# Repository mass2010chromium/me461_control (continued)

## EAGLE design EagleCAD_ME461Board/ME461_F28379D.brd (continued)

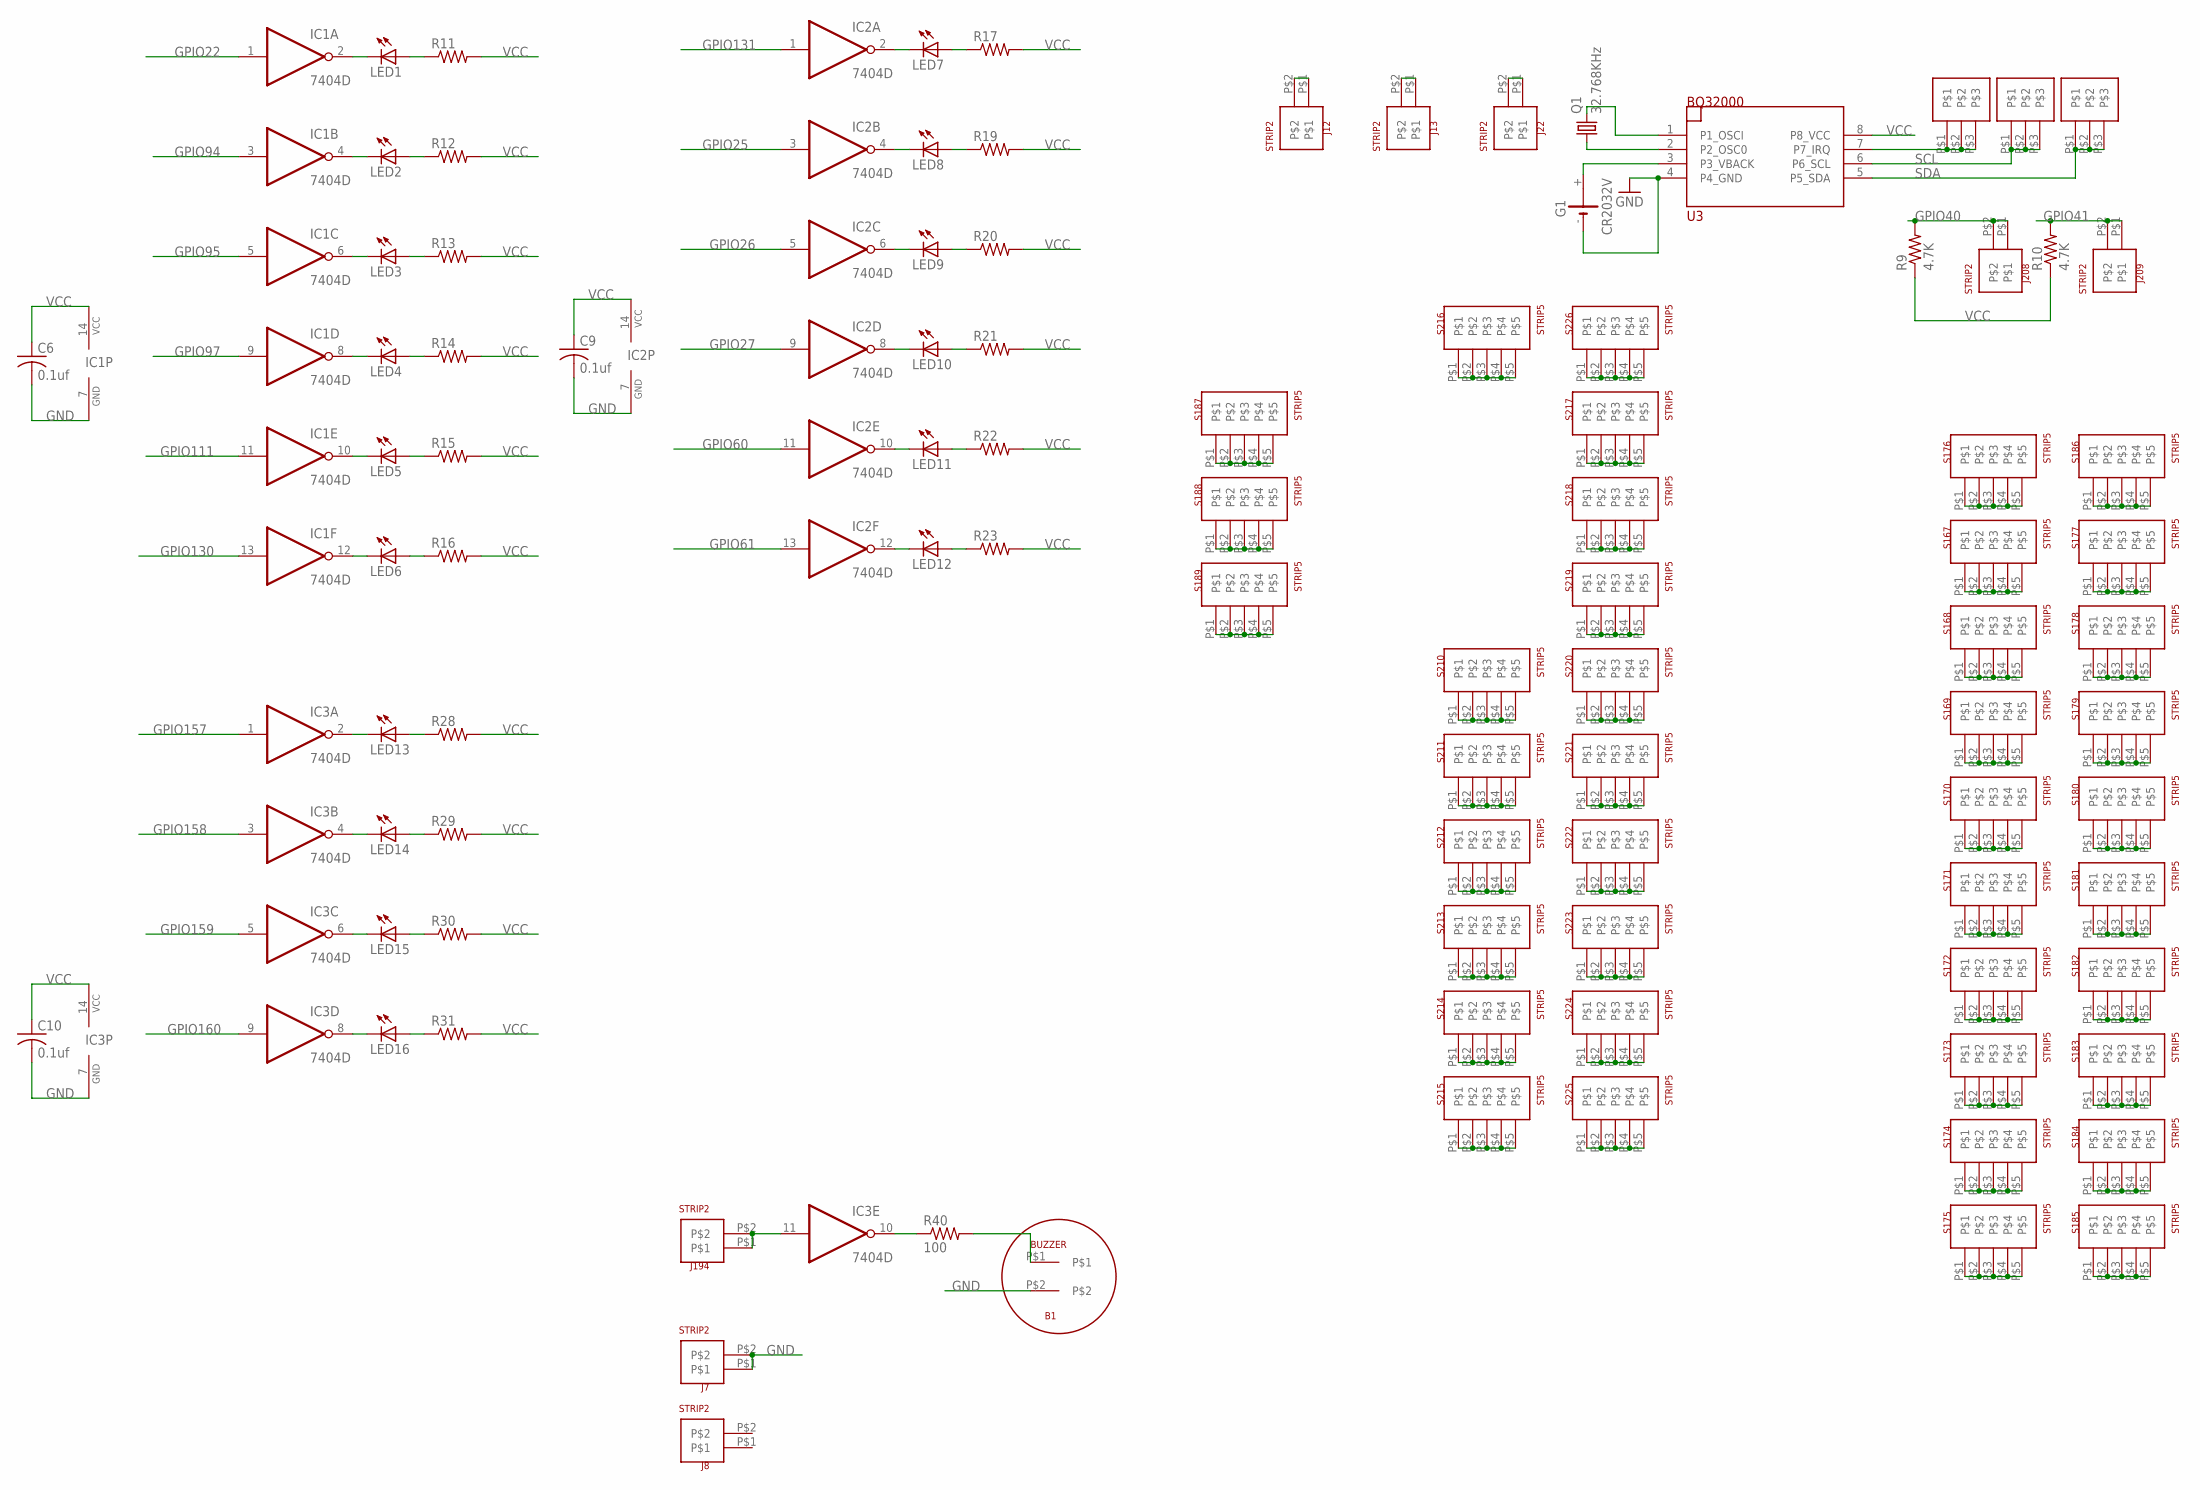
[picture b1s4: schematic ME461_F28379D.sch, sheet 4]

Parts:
B1: BUZZER
C6, C9, C10: 0.1uf; C1206
G1: CR2032V
IC1, IC2, IC3: 7404D; SO14
J1, J2, J3: STRIP3
J7, J8, J12, J13, J22, J194, J208, J209: STRIP2
LED1, LED2, LED3, LED4, LED5, LED6, LED7, LED8, LED9, LED10, LED11, LED12, LED13, LED14, LED15, LED16: LEDCHIPLED_1206; CHIPLED_1206
Q1: 32.768KHz; TC26H
R9, R10: 4.7K; R1206
R11, R12, R13, R14, R15, R16, R17, R19, R20, R21, R22, R23, R28, R29, R30, R31: R-US_R1206; R1206
R40: 100; R1206
S167, S168, S169, S170, S171, S172, S173, S174, S175, S176, S177, S178, S179, S180, S181, S182, S183, S184, S185, S186, S187, S188, S189, S210, S211, S212, S213, S214, S215, S216, S217, S218, S219, S220, S221, S222, S223, S224, S225, S226: STRIP5
U3: BQ32000; SO08

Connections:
GND: B1.P$2, C6.2, C9.2, C10.2, G1.-, IC1.7 (GND), IC2.7 (GND), IC3.7 (GND), J7.P$1, J7.P$2, U3.4 (P4_GND); also elsewhere on the board
GPIO22: IC1.1 (I); also elsewhere on the board
GPIO25: IC2.3 (I); also elsewhere on the board
GPIO26: IC2.5 (I); also elsewhere on the board
GPIO27: IC2.9 (I); also elsewhere on the board
GPIO40: J208.P$1, J208.P$2, R9.2; also elsewhere on the board
GPIO41: J209.P$1, J209.P$2, R10.2; also elsewhere on the board
GPIO60: IC2.11 (I); also elsewhere on the board
GPIO61: IC2.13 (I); also elsewhere on the board
GPIO94: IC1.3 (I); also elsewhere on the board
GPIO95: IC1.5 (I); also elsewhere on the board
GPIO97: IC1.9 (I); also elsewhere on the board
GPIO111: IC1.11 (I); also elsewhere on the board
GPIO130: IC1.13 (I); also elsewhere on the board
GPIO131: IC2.1 (I); also elsewhere on the board
GPIO157: IC3.1 (I); also elsewhere on the board
GPIO158: IC3.3 (I); also elsewhere on the board
GPIO159: IC3.5 (I); also elsewhere on the board
GPIO160: IC3.9 (I); also elsewhere on the board
unnamed: J12.P$1, J12.P$2
unnamed: J13.P$1, J13.P$2
unnamed: J22.P$1, J22.P$2
unnamed: IC3.10 (O), R40.1
unnamed: B1.P$1, R40.2
unnamed: Q1.1, U3.2 (P2_OSC0)
unnamed: Q1.2, U3.1 (P1_OSCI)
unnamed: J1.P$1, J1.P$2, J1.P$3, U3.7 (P7_IRQ)
unnamed: G1.+, U3.3 (P3_VBACK)
unnamed: IC2.2 (O), LED7.C
unnamed: LED7.A, R17.1
unnamed: IC2.4 (O), LED8.C
unnamed: LED8.A, R19.1
unnamed: IC2.6 (O), LED9.C
unnamed: S167.P$1, S167.P$2, S167.P$3, S167.P$4, S167.P$5
unnamed: S168.P$1, S168.P$2, S168.P$3, S168.P$4, S168.P$5
unnamed: S169.P$1, S169.P$2, S169.P$3, S169.P$4, S169.P$5
unnamed: S170.P$1, S170.P$2, S170.P$3, S170.P$4, S170.P$5
unnamed: S171.P$1, S171.P$2, S171.P$3, S171.P$4, S171.P$5
unnamed: S172.P$1, S172.P$2, S172.P$3, S172.P$4, S172.P$5
unnamed: S173.P$1, S173.P$2, S173.P$3, S173.P$4, S173.P$5
unnamed: S174.P$1, S174.P$2, S174.P$3, S174.P$4, S174.P$5
unnamed: S175.P$1, S175.P$2, S175.P$3, S175.P$4, S175.P$5
unnamed: S176.P$1, S176.P$2, S176.P$3, S176.P$4, S176.P$5
unnamed: S177.P$1, S177.P$2, S177.P$3, S177.P$4, S177.P$5
unnamed: S178.P$1, S178.P$2, S178.P$3, S178.P$4, S178.P$5
unnamed: S179.P$1, S179.P$2, S179.P$3, S179.P$4, S179.P$5
unnamed: S180.P$1, S180.P$2, S180.P$3, S180.P$4, S180.P$5
unnamed: S181.P$1, S181.P$2, S181.P$3, S181.P$4, S181.P$5
unnamed: S182.P$1, S182.P$2, S182.P$3, S182.P$4, S182.P$5
unnamed: S183.P$1, S183.P$2, S183.P$3, S183.P$4, S183.P$5
unnamed: S184.P$1, S184.P$2, S184.P$3, S184.P$4, S184.P$5
unnamed: S185.P$1, S185.P$2, S185.P$3, S185.P$4, S185.P$5
unnamed: S186.P$1, S186.P$2, S186.P$3, S186.P$4, S186.P$5
unnamed: S187.P$1, S187.P$2, S187.P$3, S187.P$4, S187.P$5
unnamed: S188.P$1, S188.P$2, S188.P$3, S188.P$4, S188.P$5
unnamed: S189.P$1, S189.P$2, S189.P$3, S189.P$4, S189.P$5
unnamed: S210.P$1, S210.P$2, S210.P$3, S210.P$4, S210.P$5
unnamed: S211.P$1, S211.P$2, S211.P$3, S211.P$4, S211.P$5
unnamed: S212.P$1, S212.P$2, S212.P$3, S212.P$4, S212.P$5
unnamed: S213.P$1, S213.P$2, S213.P$3, S213.P$4, S213.P$5
unnamed: S214.P$1, S214.P$2, S214.P$3, S214.P$4, S214.P$5
unnamed: S215.P$1, S215.P$2, S215.P$3, S215.P$4, S215.P$5
unnamed: S216.P$1, S216.P$2, S216.P$3, S216.P$4, S216.P$5
unnamed: S217.P$1, S217.P$2, S217.P$3, S217.P$4, S217.P$5
unnamed: S218.P$1, S218.P$2, S218.P$3, S218.P$4, S218.P$5
unnamed: S219.P$1, S219.P$2, S219.P$3, S219.P$4, S219.P$5
unnamed: S220.P$1, S220.P$2, S220.P$3, S220.P$4, S220.P$5
unnamed: S221.P$1, S221.P$2, S221.P$3, S221.P$4, S221.P$5
unnamed: S222.P$1, S222.P$2, S222.P$3, S222.P$4, S222.P$5
unnamed: S223.P$1, S223.P$2, S223.P$3, S223.P$4, S223.P$5
unnamed: S224.P$1, S224.P$2, S224.P$3, S224.P$4, S224.P$5
unnamed: S225.P$1, S225.P$2, S225.P$3, S225.P$4, S225.P$5
unnamed: S226.P$1, S226.P$2, S226.P$3, S226.P$4, S226.P$5
unnamed: IC1.2 (O), LED1.C
unnamed: LED1.A, R11.1
unnamed: IC1.4 (O), LED2.C
unnamed: LED2.A, R12.1
unnamed: IC1.6 (O), LED3.C
unnamed: LED3.A, R13.1
unnamed: IC1.8 (O), LED4.C
unnamed: LED4.A, R14.1
unnamed: IC1.10 (O), LED5.C
unnamed: LED5.A, R15.1
unnamed: IC1.12 (O), LED6.C
unnamed: LED6.A, R16.1
unnamed: LED9.A, R20.1
unnamed: IC2.8 (O), LED10.C
unnamed: LED10.A, R21.1
unnamed: IC2.10 (O), LED11.C
unnamed: LED11.A, R22.1
unnamed: IC2.12 (O), LED12.C
unnamed: LED12.A, R23.1
unnamed: IC3.2 (O), LED13.C
unnamed: LED13.A, R28.1
unnamed: IC3.4 (O), LED14.C
unnamed: LED14.A, R29.1
unnamed: IC3.6 (O), LED15.C
unnamed: LED15.A, R30.1
unnamed: IC3.8 (O), LED16.C
unnamed: LED16.A, R31.1
unnamed: IC3.11 (I), J194.P$1, J194.P$2
SCL: J2.P$1, J2.P$2, J2.P$3, U3.6 (P6_SCL)
SDA: J3.P$1, J3.P$2, J3.P$3, U3.5 (P5_SDA)
VCC: C6.1, C9.1, C10.1, IC1.14 (VCC), IC2.14 (VCC), IC3.14 (VCC), R9.1, R10.1, R11.2, R12.2, R13.2, R14.2, R15.2, R16.2, R17.2, R19.2, R20.2, R21.2, R22.2, R23.2, R28.2, R29.2, R30.2, R31.2, U3.8 (P8_VCC); also elsewhere on the board

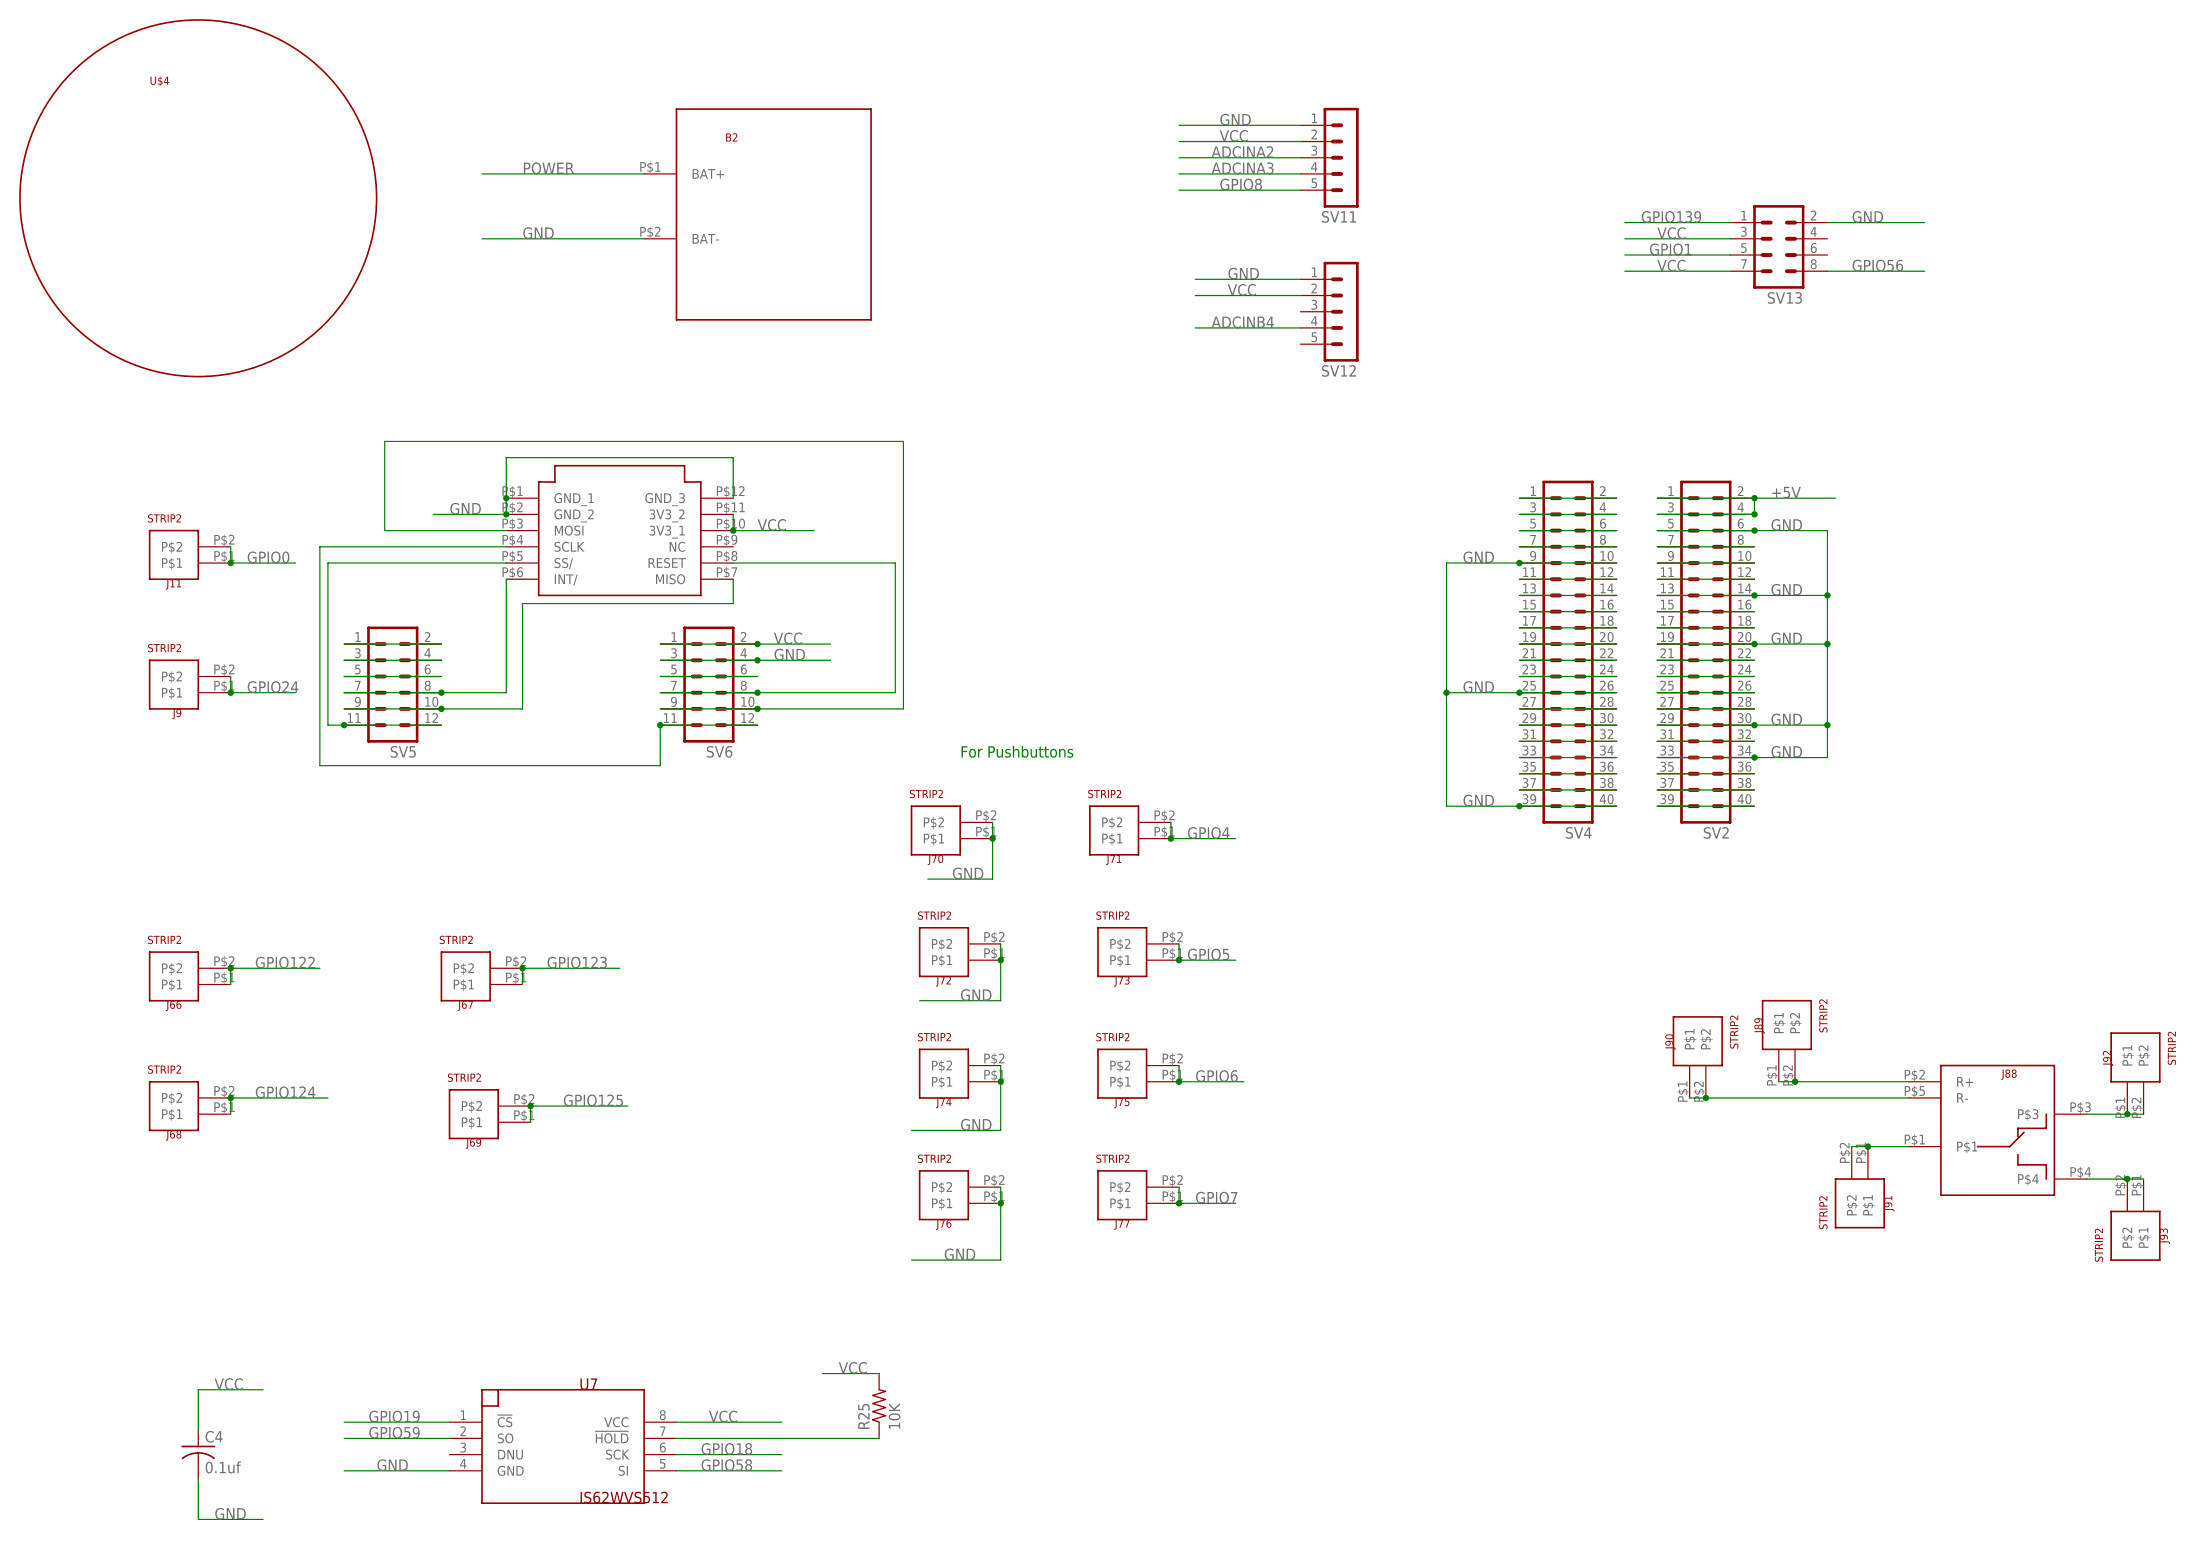
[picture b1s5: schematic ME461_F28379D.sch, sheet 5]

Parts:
B2: BATTERY_4AA_HOLDER
C4: 0.1uf; C1206
ETH1: USR_ES1_W5500
J9, J11, J66, J67, J68, J69, J70, J71, J72, J73, J74, J75, J76, J77, J89, J90, J91, J92, J93: STRIP2
J88: RELAY_JQC-3F_5V
R25: 10K; M1206
SV2, SV4: MA20-2
SV5, SV6: MA06-2
SV11, SV12: MA05-1
SV13: MA04-2
U7: IS62WVS512; SO08
U$4: CASTERWHEEL

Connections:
+5V: SV2.1, SV2.2, SV2.3, SV2.4; also elsewhere on the board
ADCINA2: SV11.3; also elsewhere on the board
ADCINA3: SV11.4; also elsewhere on the board
ADCINB4: SV12.4; also elsewhere on the board
GND: B2.P$2 (BAT-), C4.2, ETH1.P$1 (GND_1), ETH1.P$2 (GND_2), ETH1.P$12 (GND_3), J70.P$1, J70.P$2, J72.P$1, J72.P$2, J74.P$1, J74.P$2, J76.P$1, J76.P$2, SV2.5, SV2.6, SV2.13, SV2.14, SV2.19, SV2.20, SV2.29, SV2.30, SV2.33, SV2.34, SV4.9, SV4.10, SV4.25, SV4.26, SV4.39, SV4.40, SV6.3, SV6.4, SV11.1, SV12.1, SV13.2, U7.4 (GND); also elsewhere on the board
GPIO0: J11.P$1, J11.P$2; also elsewhere on the board
GPIO1: SV13.5; also elsewhere on the board
GPIO4: J71.P$1, J71.P$2; also elsewhere on the board
GPIO5: J73.P$1, J73.P$2; also elsewhere on the board
GPIO6: J75.P$1, J75.P$2; also elsewhere on the board
GPIO7: J77.P$1, J77.P$2; also elsewhere on the board
GPIO8: SV11.5; also elsewhere on the board
GPIO18: U7.6 (SCK); also elsewhere on the board
GPIO19: U7.1 (!CS); also elsewhere on the board
GPIO24: J9.P$1, J9.P$2; also elsewhere on the board
GPIO56: SV13.8; also elsewhere on the board
GPIO58: U7.5 (SI); also elsewhere on the board
GPIO59: U7.2 (SO); also elsewhere on the board
GPIO122: J66.P$1, J66.P$2; also elsewhere on the board
GPIO123: J67.P$1, J67.P$2; also elsewhere on the board
GPIO124: J68.P$1, J68.P$2; also elsewhere on the board
GPIO125: J69.P$1, J69.P$2; also elsewhere on the board
GPIO139: SV13.1; also elsewhere on the board
unnamed: R25.1, U7.7 (!HOLD)
unnamed: SV4.1, SV4.2
unnamed: SV5.1, SV5.2
unnamed: SV5.3, SV5.4
unnamed: SV5.5, SV5.6
unnamed: SV4.3, SV4.4
unnamed: SV4.5, SV4.6
unnamed: SV4.7, SV4.8
unnamed: ETH1.P$6 (INT/), SV5.7, SV5.8
unnamed: SV4.11, SV4.12
unnamed: SV4.13, SV4.14
unnamed: SV4.15, SV4.16
unnamed: SV4.17, SV4.18
unnamed: SV4.19, SV4.20
unnamed: SV4.21, SV4.22
unnamed: SV4.23, SV4.24
unnamed: ETH1.P$7 (MISO), SV5.9, SV5.10
unnamed: SV4.27, SV4.28
unnamed: SV4.29, SV4.30
unnamed: SV4.31, SV4.32
unnamed: SV4.33, SV4.34
unnamed: SV4.35, SV4.36
unnamed: SV4.37, SV4.38
unnamed: ETH1.P$5 (SS/), SV5.11, SV5.12
unnamed: SV2.39, SV2.40
unnamed: SV2.37, SV2.38
unnamed: SV2.35, SV2.36
unnamed: SV2.31, SV2.32
unnamed: SV2.27, SV2.28
unnamed: SV2.25, SV2.26
unnamed: SV2.23, SV2.24
unnamed: SV2.21, SV2.22
unnamed: SV6.5, SV6.6
unnamed: SV2.17, SV2.18
unnamed: SV2.15, SV2.16
unnamed: ETH1.P$8 (RESET), SV6.7, SV6.8
unnamed: SV2.11, SV2.12
unnamed: SV2.9, SV2.10
unnamed: SV2.7, SV2.8
unnamed: ETH1.P$3 (MOSI), SV6.9, SV6.10
unnamed: ETH1.P$4 (SCLK), SV6.11, SV6.12
unnamed: J88.P$2 (R+), J89.P$1, J89.P$2
unnamed: J88.P$5 (R-), J90.P$1, J90.P$2
unnamed: J88.P$1, J91.P$1, J91.P$2
unnamed: J88.P$3, J92.P$1, J92.P$2
unnamed: J88.P$4, J93.P$1, J93.P$2
POWER: B2.P$1 (BAT+); also elsewhere on the board
VCC: C4.1, ETH1.P$10 (3V3_1), ETH1.P$11 (3V3_2), R25.2, SV6.1, SV6.2, SV11.2, SV12.2, SV13.3, SV13.7, U7.8 (VCC); also elsewhere on the board

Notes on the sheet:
For Pushbuttons

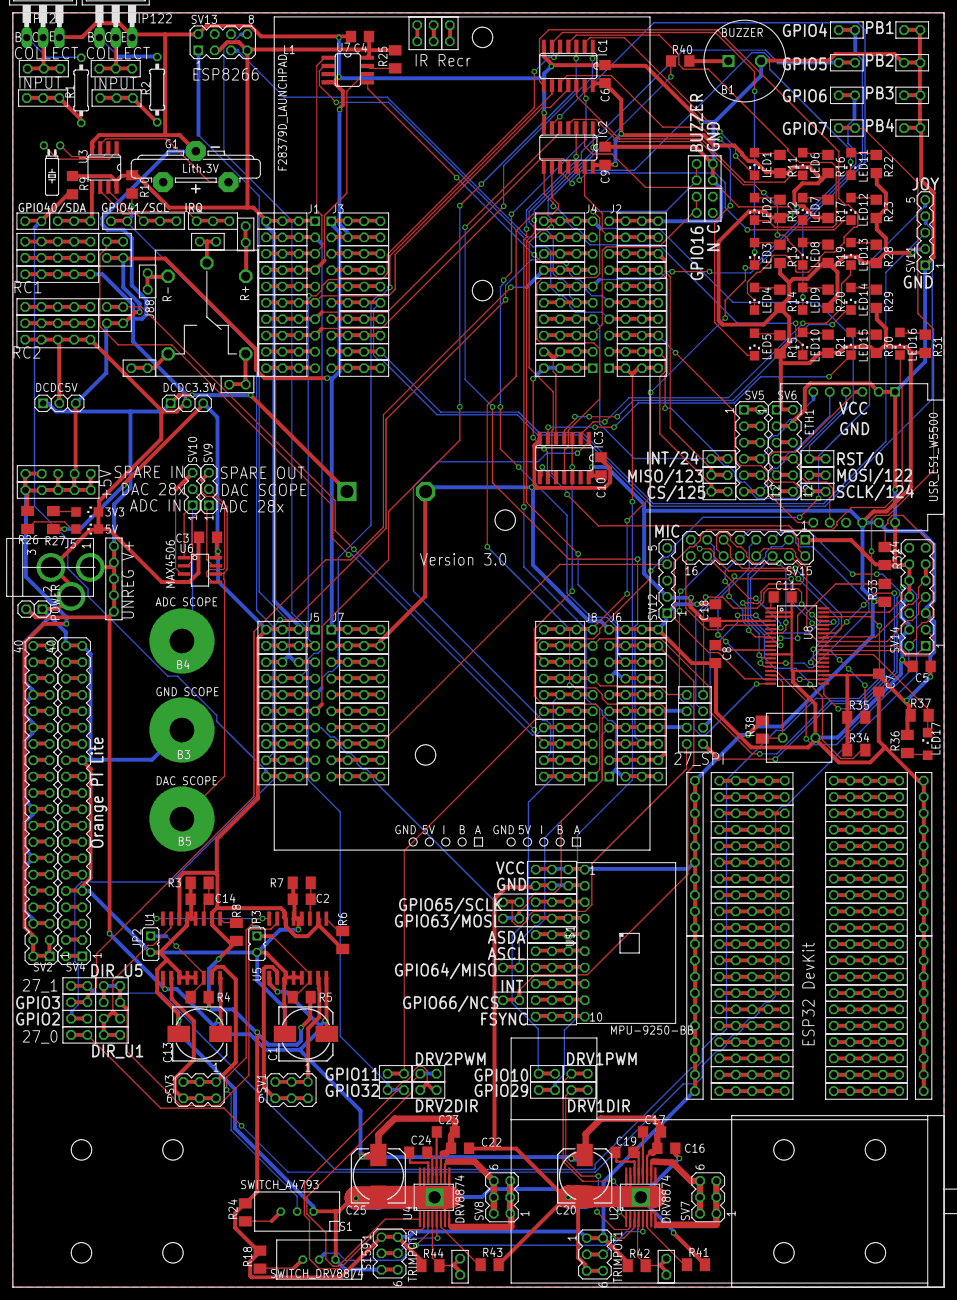
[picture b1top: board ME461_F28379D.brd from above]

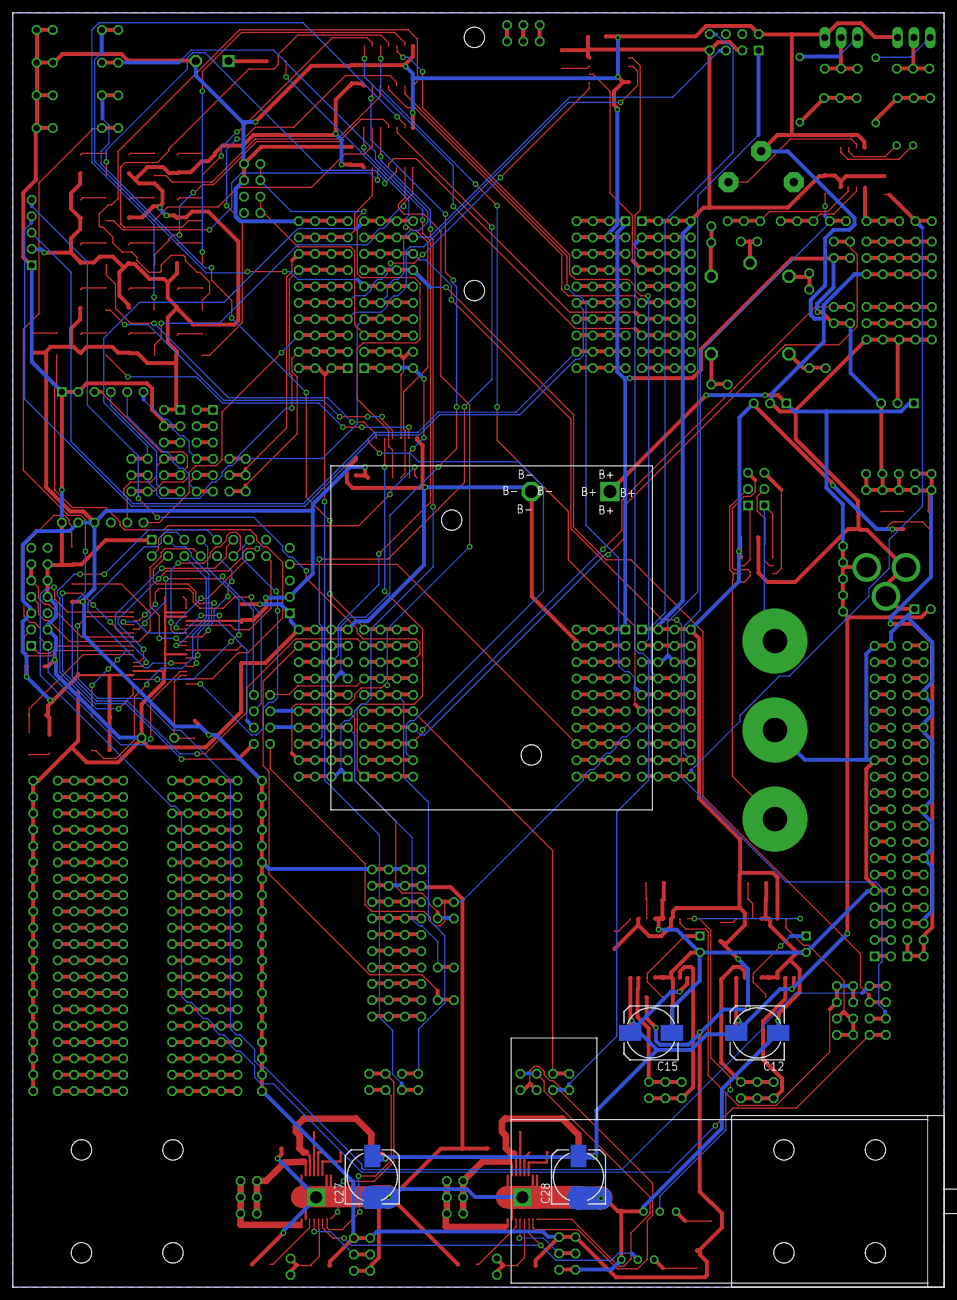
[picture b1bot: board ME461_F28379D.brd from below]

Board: 2 copper layers, 144.8 x 198.1 mm, 349 parts (6 on the bottom side), 299 nets.

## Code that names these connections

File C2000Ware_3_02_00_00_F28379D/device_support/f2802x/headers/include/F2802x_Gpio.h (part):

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//
struct GPA1_BITS
{                                // bits   description
    uint16_t GPIO0:2;            // 1:0    GPIO0
    uint16_t GPIO1:2;            // 3:2    GPIO1
    uint16_t GPIO2:2;            // 5:4    GPIO2
    uint16_t GPIO3:2;            // 7:6    GPIO3
    uint16_t GPIO4:2;            // 9:8    GPIO4
    uint16_t GPIO5:2;            // 11:10  GPIO5
    uint16_t GPIO6:2;            // 13:12  GPIO6
    uint16_t GPIO7:2;            // 15:14  GPIO7
    uint16_t GPIO8:2;            // 17:16  GPIO8
    uint16_t GPIO9:2;            // 19:18  GPIO9
    uint16_t GPIO10:2;           // 21:20  GPIO10
    uint16_t GPIO11:2;           // 23:22  GPIO11
    uint16_t GPIO12:2;           // 25:24  GPIO12
    uint16_t GPIO13:2;           // 27:26  GPIO13
    uint16_t GPIO14:2;           // 29:28  GPIO14
    uint16_t GPIO15:2;           // 31:30  GPIO15
};

struct GPA2_BITS
{                                // bits   description
    uint16_t GPIO16:2;           // 1:0    GPIO16
    uint16_t GPIO17:2;           // 3:2    GPIO17
    uint16_t GPIO18:2;           // 5:4    GPIO18
    uint16_t GPIO19:2;           // 7:6    GPIO19
    uint16_t GPIO20:2;           // 9:8    GPIO20
    uint16_t GPIO21:2;           // 11:10  GPIO21
    uint16_t GPIO22:2;           // 13:12  GPIO22
    uint16_t GPIO23:2;           // 15:14  GPIO23
    uint16_t GPIO24:2;           // 17:16  GPIO24
    uint16_t GPIO25:2;           // 19:18  GPIO25
    uint16_t GPIO26:2;           // 21:20  GPIO26
    uint16_t GPIO27:2;           // 23:22  GPIO27
    uint16_t GPIO28:2;           // 25:24  GPIO28
    uint16_t GPIO29:2;           // 27:26  GPIO29
    uint16_t GPIO30:2;           // 29:28  GPIO30
    uint16_t GPIO31:2;           // 31:30  GPIO31
};

struct GPB1_BITS
{                               // bits   description
    uint16_t GPIO32:2;           // 1:0    GPIO32
    uint16_t GPIO33:2;           // 3:2    GPIO33
    uint16_t GPIO34:2;           // 5:4    GPIO34
    uint16_t GPIO35:2;           // 7:6    GPIO35
    uint16_t GPIO36:2;           // 9:8    GPIO36
    uint16_t GPIO37:2;           // 11:10  GPIO37
    uint16_t GPIO38:2;           // 13:12  GPIO38
    uint16_t rsvd1:2;            // 15:14  reserved
    uint16_t rsvd2:16;           // 31:16  reserved
};

struct AIO_BITS
{                               // bits   description
    uint16_t rsvd1:2;           // 1:0    GPIO0
    uint16_t rsvd2:2;           // 3:2    GPIO1
    uint16_t AIO2:2;            // 5:4    GPIO2
    uint16_t rsvd3:2;           // 7:6    GPIO3
    uint16_t AIO4:2;            // 9:8    GPIO4
    uint16_t rsvd4:2;           // 11:10  GPIO5
    uint16_t AIO6:2;            // 13:12  GPIO6
    uint16_t rsvd5:2;           // 15:14  GPIO7
    uint16_t rsvd6:2;           // 17:16  GPIO8
    uint16_t rsvd7:2;           // 19:18  GPIO9
    uint16_t AIO10:2;           // 21:20  GPIO10
    uint16_t rsvd8:2;           // 23:22  GPIO11
    uint16_t AIO12:2;           // 25:24  GPIO12
    uint16_t rsvd9:2;           // 27:26  GPIO13
    uint16_t AIO14:2;           // 29:28  GPIO14
    uint16_t rsvd10:2;          // 31:30  GPIO15
};

union GPA1_REG
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//
struct GPADAT_BITS
{                                // bits   description
    uint16_t GPIO0:1;            // 0      GPIO0
    uint16_t GPIO1:1;            // 1      GPIO1
    uint16_t GPIO2:1;            // 2      GPIO2
    uint16_t GPIO3:1;            // 3      GPIO3
    uint16_t GPIO4:1;            // 4      GPIO4
    uint16_t GPIO5:1;            // 5      GPIO5
    uint16_t GPIO6:1;            // 6      GPIO6
    uint16_t GPIO7:1;            // 7      GPIO7
    uint16_t GPIO8:1;            // 8      GPIO8
    uint16_t GPIO9:1;            // 9      GPIO9
    uint16_t GPIO10:1;           // 10     GPIO10
    uint16_t GPIO11:1;           // 11     GPIO11
    uint16_t GPIO12:1;           // 12     GPIO12
    uint16_t GPIO13:1;           // 13     GPIO13
    uint16_t GPIO14:1;           // 14     GPIO14
    uint16_t GPIO15:1;           // 15     GPIO15
    uint16_t GPIO16:1;           // 16     GPIO16
    uint16_t GPIO17:1;           // 17     GPIO17
    uint16_t GPIO18:1;           // 18     GPIO18
    uint16_t GPIO19:1;           // 19     GPIO19
    uint16_t GPIO20:1;           // 20     GPIO20
    uint16_t GPIO21:1;           // 21     GPIO21
    uint16_t GPIO22:1;           // 22     GPIO22
    uint16_t GPIO23:1;           // 23     GPIO23
    uint16_t GPIO24:1;           // 24     GPIO24
    uint16_t GPIO25:1;           // 25     GPIO25
    uint16_t GPIO26:1;           // 26     GPIO26
    uint16_t GPIO27:1;           // 27     GPIO27
    uint16_t GPIO28:1;           // 28     GPIO28
    uint16_t GPIO29:1;           // 29     GPIO29
    uint16_t GPIO30:1;           // 30     GPIO30
    uint16_t GPIO31:1;           // 31     GPIO31
};

struct GPBDAT_BITS
{                                // bits   description
    uint16_t GPIO32:1;           // 0      GPIO32
    uint16_t GPIO33:1;           // 1      GPIO33
    uint16_t GPIO34:1;           // 2      GPIO34
    uint16_t GPIO35:1;           // 3      GPIO35
    uint16_t GPIO36:1;           // 4      GPIO36
    uint16_t GPIO37:1;           // 5      GPIO37
    uint16_t GPIO38:1;           // 6      GPIO38
    uint16_t rsvd1:9;            // 15:7   reserved
    uint16_t rsvd2:16;           // 31:16  reserved
};
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
struct GPIO_CTRL_REGS
{
    union  GPACTRL_REG  GPACTRL;   // GPIO A Control Register (GPIO0 to 31)
    
    //
    // GPIO A Qualifier Select 1 Register (GPIO0 to 15)
    //
    union  GPA1_REG     GPAQSEL1;
    
    //
    // GPIO A Qualifier Select 2 Register (GPIO16 to 31)
    //
    union  GPA2_REG     GPAQSEL2;
    
    union  GPA1_REG     GPAMUX1;   // GPIO A Mux 1 Register (GPIO0 to 15)
    union  GPA2_REG     GPAMUX2;   // GPIO A Mux 2 Register (GPIO16 to 31)
    union  GPADAT_REG   GPADIR;    // GPIO A Direction Register (GPIO0 to 31)
    
    //
    // GPIO A Pull Up Disable Register (GPIO0 to 31)
    //
    union  GPADAT_REG   GPAPUD;    
    
    uint32_t            rsvd1;     // reserved
    union  GPBCTRL_REG  GPBCTRL;   // GPIO B Control Register (GPIO32 to 38)
    
    //
    // GPIO B Qualifier Select 1 Register (GPIO32 to 38)
    //
    union  GPB1_REG     GPBQSEL1;
    
    uint32_t            rsvd2;     // reserved
    union  GPB1_REG     GPBMUX1;   // GPIO B Mux 1 Register (GPIO32 to 38)
    uint32_t            rsvd3;     // reserved
    
    //
    // GPIO B Direction Register (GPIO32 to 38)
    //
    union  GPBDAT_REG   GPBDIR;
    
    //
    // GPIO B Pull Up Disable Register (GPIO32 to 38)
    //
    union  GPBDAT_REG   GPBPUD;
    uint16_t            rsvd4[24]; // reserved
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
struct GPIO_DATA_REGS 
{
    union  GPADAT_REG       GPADAT;    // GPIO Data Register (GPIO0 to 31)
    
    //
    // GPIO Data Set Register (GPIO0 to 31)
    //
    union  GPADAT_REG       GPASET;
    
    //
    // GPIO Data Clear Register (GPIO0 to 31)
    //
    union  GPADAT_REG       GPACLEAR;
    
    //
    // GPIO Data Toggle Register (GPIO0 to 31)
    //
    union  GPADAT_REG       GPATOGGLE;
    
    union  GPBDAT_REG       GPBDAT;   // GPIO Data Register (GPIO32 to 38)
    
    //
    // GPIO Data Set Register (GPIO32 to 38)
    //
    union  GPBDAT_REG       GPBSET;
    
    
    //
    // GPIO Data Clear Register (GPIO32 to 38)
    //
    union  GPBDAT_REG       GPBCLEAR;
    
    //
    // GPIO Data Toggle Register (GPIO32 to 38)
    //
    union  GPBDAT_REG       GPBTOGGLE; 
    
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
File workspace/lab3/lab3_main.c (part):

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
    // Disable pullup on epwm pins
    EALLOW; // Below are protected registers
    GpioCtrlRegs.GPAPUD.bit.GPIO2 = 1; // For EPWM2A
    GpioCtrlRegs.GPAPUD.bit.GPIO3 = 1; // For EPWM2B
    GpioCtrlRegs.GPAPUD.bit.GPIO14 = 1; // For EPWM8A
    GpioCtrlRegs.GPAPUD.bit.GPIO15 = 1; // For EPWM8B
    GpioCtrlRegs.GPAPUD.bit.GPIO16 = 1; // For EPWM9A
    GpioCtrlRegs.GPAPUD.bit.GPIO22 = 1; // For EPWM12A
    EDIS;
	
	// Blue LED on LaunchPad
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	// Red LED on LaunchPad
    GPIO_SetupPinMux(34, GPIO_MUX_CPU1, 0);
    GPIO_SetupPinOptions(34, GPIO_OUTPUT, GPIO_PUSHPULL);
    GpioDataRegs.GPBSET.bit.GPIO34 = 1;

	// LED1 and PWM Pin
    // GPIO_SetupPinMux(22, GPIO_MUX_CPU1, 0);
    // GPIO_SetupPinOptions(22, GPIO_OUTPUT, GPIO_PUSHPULL);
    // GpioDataRegs.GPACLEAR.bit.GPIO22 = 1;
    GPIO_SetupPinMux(22, GPIO_MUX_CPU1, 5); // pin 22 to EPWM12A
    GPIO_SetupPinOptions(22, GPIO_OUTPUT, GPIO_PUSHPULL);
    setupPWM(12, &pwm12, 5000);
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	// LED2
    GPIO_SetupPinMux(94, GPIO_MUX_CPU1, 0);
    GPIO_SetupPinOptions(94, GPIO_OUTPUT, GPIO_PUSHPULL);
    GpioDataRegs.GPCCLEAR.bit.GPIO94 = 1;

	// LED3
    GPIO_SetupPinMux(95, GPIO_MUX_CPU1, 0);
    GPIO_SetupPinOptions(95, GPIO_OUTPUT, GPIO_PUSHPULL);
    GpioDataRegs.GPCCLEAR.bit.GPIO95 = 1;

	// LED4
    GPIO_SetupPinMux(97, GPIO_MUX_CPU1, 0);
    GPIO_SetupPinOptions(97, GPIO_OUTPUT, GPIO_PUSHPULL);
    GpioDataRegs.GPDCLEAR.bit.GPIO97 = 1;

	// LED5
    GPIO_SetupPinMux(111, GPIO_MUX_CPU1, 0);
    GPIO_SetupPinOptions(111, GPIO_OUTPUT, GPIO_PUSHPULL);
    GpioDataRegs.GPDCLEAR.bit.GPIO111 = 1;

	// LED6
    GPIO_SetupPinMux(130, GPIO_MUX_CPU1, 0);
    GPIO_SetupPinOptions(130, GPIO_OUTPUT, GPIO_PUSHPULL);
    GpioDataRegs.GPECLEAR.bit.GPIO130 = 1;

	// LED7	
    GPIO_SetupPinMux(131, GPIO_MUX_CPU1, 0);
    GPIO_SetupPinOptions(131, GPIO_OUTPUT, GPIO_PUSHPULL);
    GpioDataRegs.GPECLEAR.bit.GPIO131 = 1;

	// LED8
    GPIO_SetupPinMux(25, GPIO_MUX_CPU1, 0);
    GPIO_SetupPinOptions(25, GPIO_OUTPUT, GPIO_PUSHPULL);
    GpioDataRegs.GPACLEAR.bit.GPIO25 = 1;

	// LED9
    GPIO_SetupPinMux(26, GPIO_MUX_CPU1, 0);
    GPIO_SetupPinOptions(26, GPIO_OUTPUT, GPIO_PUSHPULL);
    GpioDataRegs.GPACLEAR.bit.GPIO26 = 1;

	// LED10
    GPIO_SetupPinMux(27, GPIO_MUX_CPU1, 0);
    GPIO_SetupPinOptions(27, GPIO_OUTPUT, GPIO_PUSHPULL);
    GpioDataRegs.GPACLEAR.bit.GPIO27 = 1;

	// LED11	
    GPIO_SetupPinMux(60, GPIO_MUX_CPU1, 0);
    GPIO_SetupPinOptions(60, GPIO_OUTPUT, GPIO_PUSHPULL);
    GpioDataRegs.GPBCLEAR.bit.GPIO60 = 1;

	// LED12	
    GPIO_SetupPinMux(61, GPIO_MUX_CPU1, 0);
    GPIO_SetupPinOptions(61, GPIO_OUTPUT, GPIO_PUSHPULL);
    GpioDataRegs.GPBCLEAR.bit.GPIO61 = 1;

	// LED13
    GPIO_SetupPinMux(157, GPIO_MUX_CPU1, 0);
    GPIO_SetupPinOptions(157, GPIO_OUTPUT, GPIO_PUSHPULL);
    GpioDataRegs.GPECLEAR.bit.GPIO157 = 1;

	// LED14
    GPIO_SetupPinMux(158, GPIO_MUX_CPU1, 0);
    GPIO_SetupPinOptions(158, GPIO_OUTPUT, GPIO_PUSHPULL);
    GpioDataRegs.GPECLEAR.bit.GPIO158 = 1;
	
	// LED15
    GPIO_SetupPinMux(159, GPIO_MUX_CPU1, 0);
    GPIO_SetupPinOptions(159, GPIO_OUTPUT, GPIO_PUSHPULL);
    GpioDataRegs.GPECLEAR.bit.GPIO159 = 1;

	// LED16
    GPIO_SetupPinMux(160, GPIO_MUX_CPU1, 0);
    GPIO_SetupPinOptions(160, GPIO_OUTPUT, GPIO_PUSHPULL);
    GpioDataRegs.GPFCLEAR.bit.GPIO160 = 1;

    //WIZNET Reset
    GPIO_SetupPinMux(0, GPIO_MUX_CPU1, 0);
    GPIO_SetupPinOptions(0, GPIO_OUTPUT, GPIO_PUSHPULL);
    GpioDataRegs.GPASET.bit.GPIO0 = 1;

    //ESP8266 Reset
    GPIO_SetupPinMux(1, GPIO_MUX_CPU1, 0);
    GPIO_SetupPinOptions(1, GPIO_OUTPUT, GPIO_PUSHPULL);
    GpioDataRegs.GPASET.bit.GPIO1 = 1;

	//SPIRAM  CS  Chip Select
    GPIO_SetupPinMux(19, GPIO_MUX_CPU1, 0);
    GPIO_SetupPinOptions(19, GPIO_OUTPUT, GPIO_PUSHPULL);
    GpioDataRegs.GPASET.bit.GPIO19 = 1;

    //DRV8874 #1 DIR  Direction
    GPIO_SetupPinMux(29, GPIO_MUX_CPU1, 0);
    GPIO_SetupPinOptions(29, GPIO_OUTPUT, GPIO_PUSHPULL);
    GpioDataRegs.GPASET.bit.GPIO29 = 1;

    //DRV8874 #2 DIR  Direction
    GPIO_SetupPinMux(32, GPIO_MUX_CPU1, 0);
    GPIO_SetupPinOptions(32, GPIO_OUTPUT, GPIO_PUSHPULL);
    GpioDataRegs.GPBSET.bit.GPIO32 = 1;

    //DAN28027  CS  Chip Select
    GPIO_SetupPinMux(9, GPIO_MUX_CPU1, 0);
    GPIO_SetupPinOptions(9, GPIO_OUTPUT, GPIO_PUSHPULL);
    GpioDataRegs.GPASET.bit.GPIO9 = 1;
	
    //MPU9250  CS  Chip Select
    GPIO_SetupPinMux(66, GPIO_MUX_CPU1, 0);
    GPIO_SetupPinOptions(66, GPIO_OUTPUT, GPIO_PUSHPULL);
    GpioDataRegs.GPCSET.bit.GPIO66 = 1;
	
	//WIZNET  CS  Chip Select
    GPIO_SetupPinMux(125, GPIO_MUX_CPU1, 0);
    GPIO_SetupPinOptions(125, GPIO_OUTPUT, GPIO_PUSHPULL);
    GpioDataRegs.GPDSET.bit.GPIO125 = 1;
	
    //PushButton 1
    GPIO_SetupPinMux(4, GPIO_MUX_CPU1, 0);
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
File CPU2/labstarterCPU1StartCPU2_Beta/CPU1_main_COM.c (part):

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    // LED1 and PWM Pin
    GPIO_SetupPinMux(22, GPIO_MUX_CPU1, 0);
    GPIO_SetupPinOptions(22, GPIO_OUTPUT, GPIO_PUSHPULL);
    GpioDataRegs.GPACLEAR.bit.GPIO22 = 1;

    // LED2
    GPIO_SetupPinMux(94, GPIO_MUX_CPU1, 0);
    GPIO_SetupPinOptions(94, GPIO_OUTPUT, GPIO_PUSHPULL);
    GpioDataRegs.GPCCLEAR.bit.GPIO94 = 1;

    // LED3
    GPIO_SetupPinMux(95, GPIO_MUX_CPU1, 0);
    GPIO_SetupPinOptions(95, GPIO_OUTPUT, GPIO_PUSHPULL);
    GpioDataRegs.GPCCLEAR.bit.GPIO95 = 1;

    // LED4
    GPIO_SetupPinMux(97, GPIO_MUX_CPU1, 0);
    GPIO_SetupPinOptions(97, GPIO_OUTPUT, GPIO_PUSHPULL);
    GpioDataRegs.GPDCLEAR.bit.GPIO97 = 1;

    // LED5
    GPIO_SetupPinMux(111, GPIO_MUX_CPU1, 0);
    GPIO_SetupPinOptions(111, GPIO_OUTPUT, GPIO_PUSHPULL);
    GpioDataRegs.GPDCLEAR.bit.GPIO111 = 1;

    // LED6
    GPIO_SetupPinMux(130, GPIO_MUX_CPU1, 0);
    GPIO_SetupPinOptions(130, GPIO_OUTPUT, GPIO_PUSHPULL);
    GpioDataRegs.GPECLEAR.bit.GPIO130 = 1;

    // LED7
    GPIO_SetupPinMux(131, GPIO_MUX_CPU1, 0);
    GPIO_SetupPinOptions(131, GPIO_OUTPUT, GPIO_PUSHPULL);
    GpioDataRegs.GPECLEAR.bit.GPIO131 = 1;

    // LED8
    GPIO_SetupPinMux(25, GPIO_MUX_CPU1, 0);
    GPIO_SetupPinOptions(25, GPIO_OUTPUT, GPIO_PUSHPULL);
    GpioDataRegs.GPACLEAR.bit.GPIO25 = 1;

    // LED9
    GPIO_SetupPinMux(26, GPIO_MUX_CPU1, 0);
    GPIO_SetupPinOptions(26, GPIO_OUTPUT, GPIO_PUSHPULL);
    GpioDataRegs.GPACLEAR.bit.GPIO26 = 1;

    // LED10
    GPIO_SetupPinMux(27, GPIO_MUX_CPU1, 0);
    GPIO_SetupPinOptions(27, GPIO_OUTPUT, GPIO_PUSHPULL);
    GpioDataRegs.GPACLEAR.bit.GPIO27 = 1;

    //ESP8266 Reset
    GPIO_SetupPinMux(1, GPIO_MUX_CPU1, 0);
    GPIO_SetupPinOptions(1, GPIO_OUTPUT, GPIO_PUSHPULL);
    GpioDataRegs.GPASET.bit.GPIO1 = 1;

    //SPIRAM  CS  Chip Select
    GPIO_SetupPinMux(19, GPIO_MUX_CPU1, 0);
    GPIO_SetupPinOptions(19, GPIO_OUTPUT, GPIO_PUSHPULL);
    GpioDataRegs.GPASET.bit.GPIO19 = 1;

    //DRV8874 #1 DIR  Direction
    GPIO_SetupPinMux(29, GPIO_MUX_CPU1, 0);
    GPIO_SetupPinOptions(29, GPIO_OUTPUT, GPIO_PUSHPULL);
    GpioDataRegs.GPASET.bit.GPIO29 = 1;

    //DRV8874 #2 DIR  Direction
    GPIO_SetupPinMux(32, GPIO_MUX_CPU1, 0);
    GPIO_SetupPinOptions(32, GPIO_OUTPUT, GPIO_PUSHPULL);
    GpioDataRegs.GPBSET.bit.GPIO32 = 1;

    //DAN28027  CS  Chip Select
    GPIO_SetupPinMux(9, GPIO_MUX_CPU1, 0);
    GPIO_SetupPinOptions(9, GPIO_OUTPUT, GPIO_PUSHPULL);
    GpioDataRegs.GPASET.bit.GPIO9 = 1;

    //MPU9250  CS  Chip Select
    GPIO_SetupPinMux(66, GPIO_MUX_CPU1, 0);
    GPIO_SetupPinOptions(66, GPIO_OUTPUT, GPIO_PUSHPULL);
    GpioDataRegs.GPCSET.bit.GPIO66 = 1;

    //WIZNET  CS  Chip Select
    GPIO_SetupPinMux(125, GPIO_MUX_CPU1, 0);
    GPIO_SetupPinOptions(125, GPIO_OUTPUT, GPIO_PUSHPULL);
    GpioDataRegs.GPDSET.bit.GPIO125 = 1;

    //PushButton 1
    GPIO_SetupPinMux(4, GPIO_MUX_CPU1, 0);
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    GPIO_SetupPinMux(8, GPIO_MUX_CPU1, 0);
    GPIO_SetupPinOptions(8, GPIO_INPUT, GPIO_PULLUP);

    //gpio52
    GPIO_SetupPinMux(52, GPIO_MUX_CPU1, 0);
    GPIO_SetupPinOptions(52, GPIO_OUTPUT, GPIO_PUSHPULL);
    GpioDataRegs.GPBSET.bit.GPIO52 = 1;


    // Red LED on LaunchPad, change ownership to CPU2
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    GPIO_SetupPinOptions(67, GPIO_OUTPUT, GPIO_PUSHPULL);

    EALLOW;
    GpioCtrlRegs.GPDPUD.bit.GPIO122 = 0; // Enable Pull-ups on SPI PINs Recommended by TI for SPI Pins
    GpioCtrlRegs.GPDPUD.bit.GPIO123 = 0;
    GpioCtrlRegs.GPDPUD.bit.GPIO124 = 0;
    GpioCtrlRegs.GPDQSEL2.bit.GPIO122 = 3; // Set prequalifier for SPI PINS
    GpioCtrlRegs.GPDQSEL2.bit.GPIO123 = 3; // The prequalifier eliminates short noise spikes
    GpioCtrlRegs.GPDQSEL2.bit.GPIO124 = 3; // by making sure the serial pin stays low for 3 clock periods.
    EDIS;

    // Clear all interrupts and initialize PIE vector table:
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//==================================================CODE FOR FUNCTIONS========================================================================
//IPC
__interrupt void CPU2toCPU1IPC0(void){
    GpioDataRegs.GPBTOGGLE.bit.GPIO52 = 1;
    GpioDataRegs.GPETOGGLE.bit.GPIO131 = 1;//led7
    //put data from cpu2 into cpu2tocpu1 array
    int i;
    for (i=0;i<4;i++) {
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
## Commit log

2021-08-29 Added workspace folder
2021-09-01 Made it more clear that the 200Mhz clock should not be changed in the ConfigCpuTimer function.
2021-09-01 Initial commit -- test
2021-09-01 Add launches to .gitignore
2021-09-01 Setup script and readme update
2021-09-01 Fix typo
2021-09-01 Add shellscript for setup for mac users
2021-09-03 Setup scripts (TODO test)
2021-09-03 Update gitignore
2021-09-03 Initial commit -- printtest
2021-09-03 Remove printtest
2021-09-10 mingw hacking
2021-09-10 name new projects correctly
2021-09-10 Lab2 files...
2021-09-10 Editing config -- got preprocessing working
2021-09-23 Added BoardTest/BoardTestwithSWI.out so students can check motor's and encoders and other items on their Board
2021-10-01 Lab 3 codes
    and some of lab 4
    refactor success (???)
2021-10-02 More refactoring, code looks acceptable now
2021-10-06 lab4 update -- finished
2021-10-13 Lab 4 changes
2021-10-16 Python script lol
2021-10-16 Project 5... kinda...
2021-11-03 project 3
2021-11-23 Added CPU2 code
2021-11-29 Added CPU2 code that now also serial_prints to SerialC and CPU1 coms with CPU2 and CP2 coms with CPU1
2021-11-29 forgot one CPU2 file
2021-11-30 Added a flag that makes CPU2 wait until CPU1 is finished initializing. Still for some reason UARTA is receiving two bytes at the beginning????
2021-12-01 odometry files
2021-12-17 Final project version of 'odometry' project (removed fudge factor... works better now)
2021-12-17 Remove unneeded files

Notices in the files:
C2000Ware_3_02_00_00_F28379D/device_support/f2802x/headers/include/F2802x_Gpio.h:
$Copyright:
Copyright (C) 2009-2020 Texas Instruments Incorporated - http://www.ti.com
